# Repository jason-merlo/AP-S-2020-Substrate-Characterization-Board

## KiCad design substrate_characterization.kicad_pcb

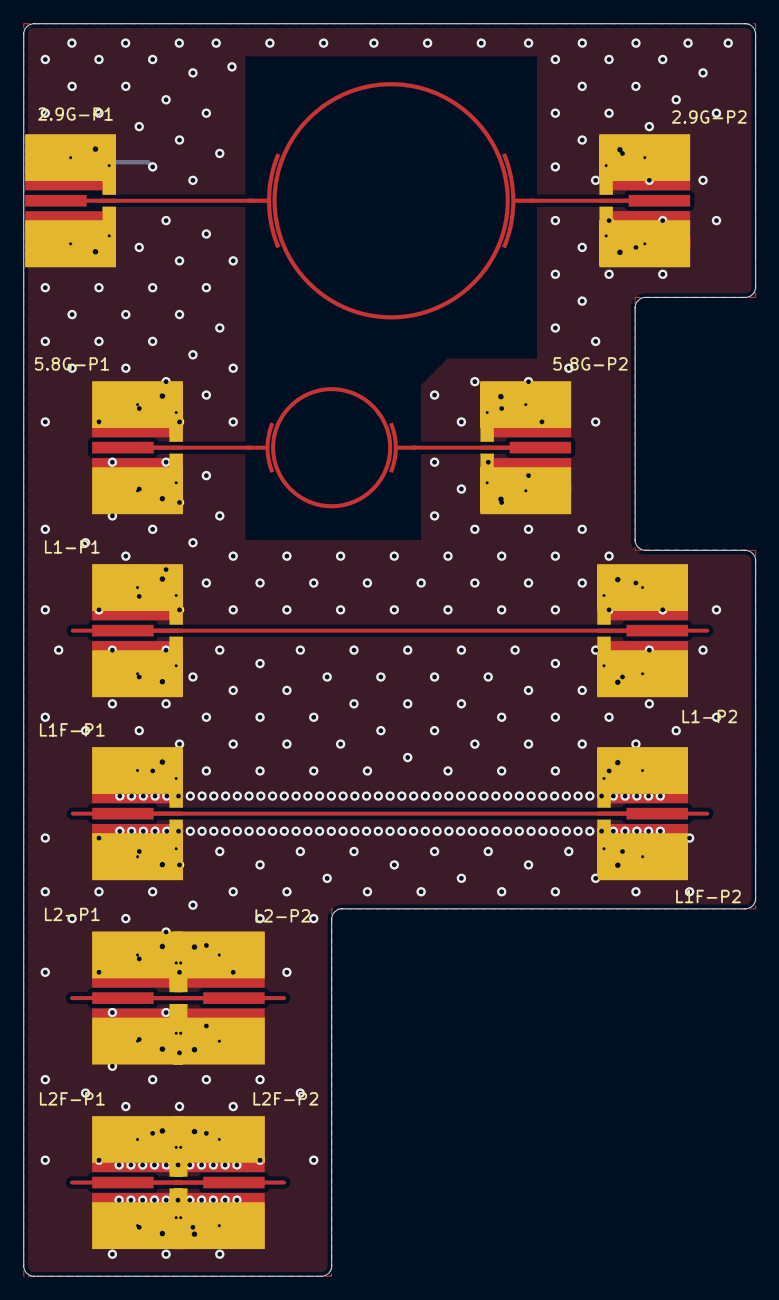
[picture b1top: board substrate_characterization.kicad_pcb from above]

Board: 4 copper layers, 62.5 x 106.9 mm, 14 parts (0 on the bottom side), 9 nets.

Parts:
FL1: 5.8GHz; 5.8G_ring_resonator_2mm
FL2: 2.9GHz; 2.9G_ring_resonator_2mm
J1: 5.8G-P1; SMA_Molex_Transition
J2: 2.9G-P1; SMA_Molex_Transition
J3: L1-P1; SMA_Molex_Transition
J4: L2-P1; SMA_Molex_Transition
J5: L1F-P1; SMA_Molex_Transition
J6: L2F-P1; SMA_Molex_Transition
J7: 5.8G-P2; SMA_Molex_Transition
J8: 2.9G-P2; SMA_Molex_Transition
J9: L1-P2; SMA_Molex_Transition
J10: L2-P2; SMA_Molex_Transition
J11: L1F-P2; SMA_Molex_Transition
J12: L2F-P2; SMA_Molex_Transition

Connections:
GND: J1.2, J2.2, J3.2, J4.2, J5.2, J6.2, J7.2, J8.2, J9.2, J10.2, J11.2, J12.2
unnamed: FL1.1, J1.1
unnamed: FL1.2, J7.1
unnamed: FL2.1, J2.1, J2.~
unnamed: FL2.2, J8.1
unnamed: J3.1, J9.1
unnamed: J4.1, J10.1
unnamed: J5.1, J11.1
unnamed: J6.1, J12.1

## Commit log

2020-03-02 Initial commit.
2020-03-09 Footprint updates for sma
